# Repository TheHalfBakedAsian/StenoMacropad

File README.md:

# The Steno Macropad
**Note: in the journal some hours are logged on one day despite being done on differnt days because I didn't realise how this worked and waited**

The Steno-style macro-pad is designed to allow multiple keystrokes simultaneously to create new outputs. With conductive sensors, it creates a thin, portable *wired* macro-pad that still serves the functions of a much larger version.

### Code functionality
The keyboard works by taking all inputs from each of the capacitive sensors and filling in their respective states into a larger bitmap to compare to a predefined table of char arrays to print out to the keyboard. I made it using char arrays of characters, because I have had difficulties otherwise, and it's pretty nice for coding to have a quick list of all your common phrases when autocorrect fails.

### Hardware Choices
The traditional Macro-pad uses mechanical switches with 2 pins but is incredibly bulky and is much more prone to breaking. I opted to work with some capacitive touch sensors, which only need a copper pad to sense, with a Xiao Esp32 C3 for more ram/flash over an Arduino Pro Micro. The added flash allows me to code in more functions for the Macro-pad than the established Pro Micro. The UDFN/USON package of my sensor chip makes it smaller lets me get away with a smaller and thin pcb.

### Schematic design
Following the provided circuit plan from the data sheet of the IC, I wired the ***Steno Macro-Pad***

### PCB placing
Originally I wanted to keep **ALL** signal traces on one side, but the size of the PCB and other traces made it so I had to use some buried vias near the back side’s copper sense pads. But who can forget adding some personal symbol in the silk screening, mine being an ace of spades. alt text The large blue squares being the copper pads on the back side.  The large blue squares being the copper pads on the back side.

## Render

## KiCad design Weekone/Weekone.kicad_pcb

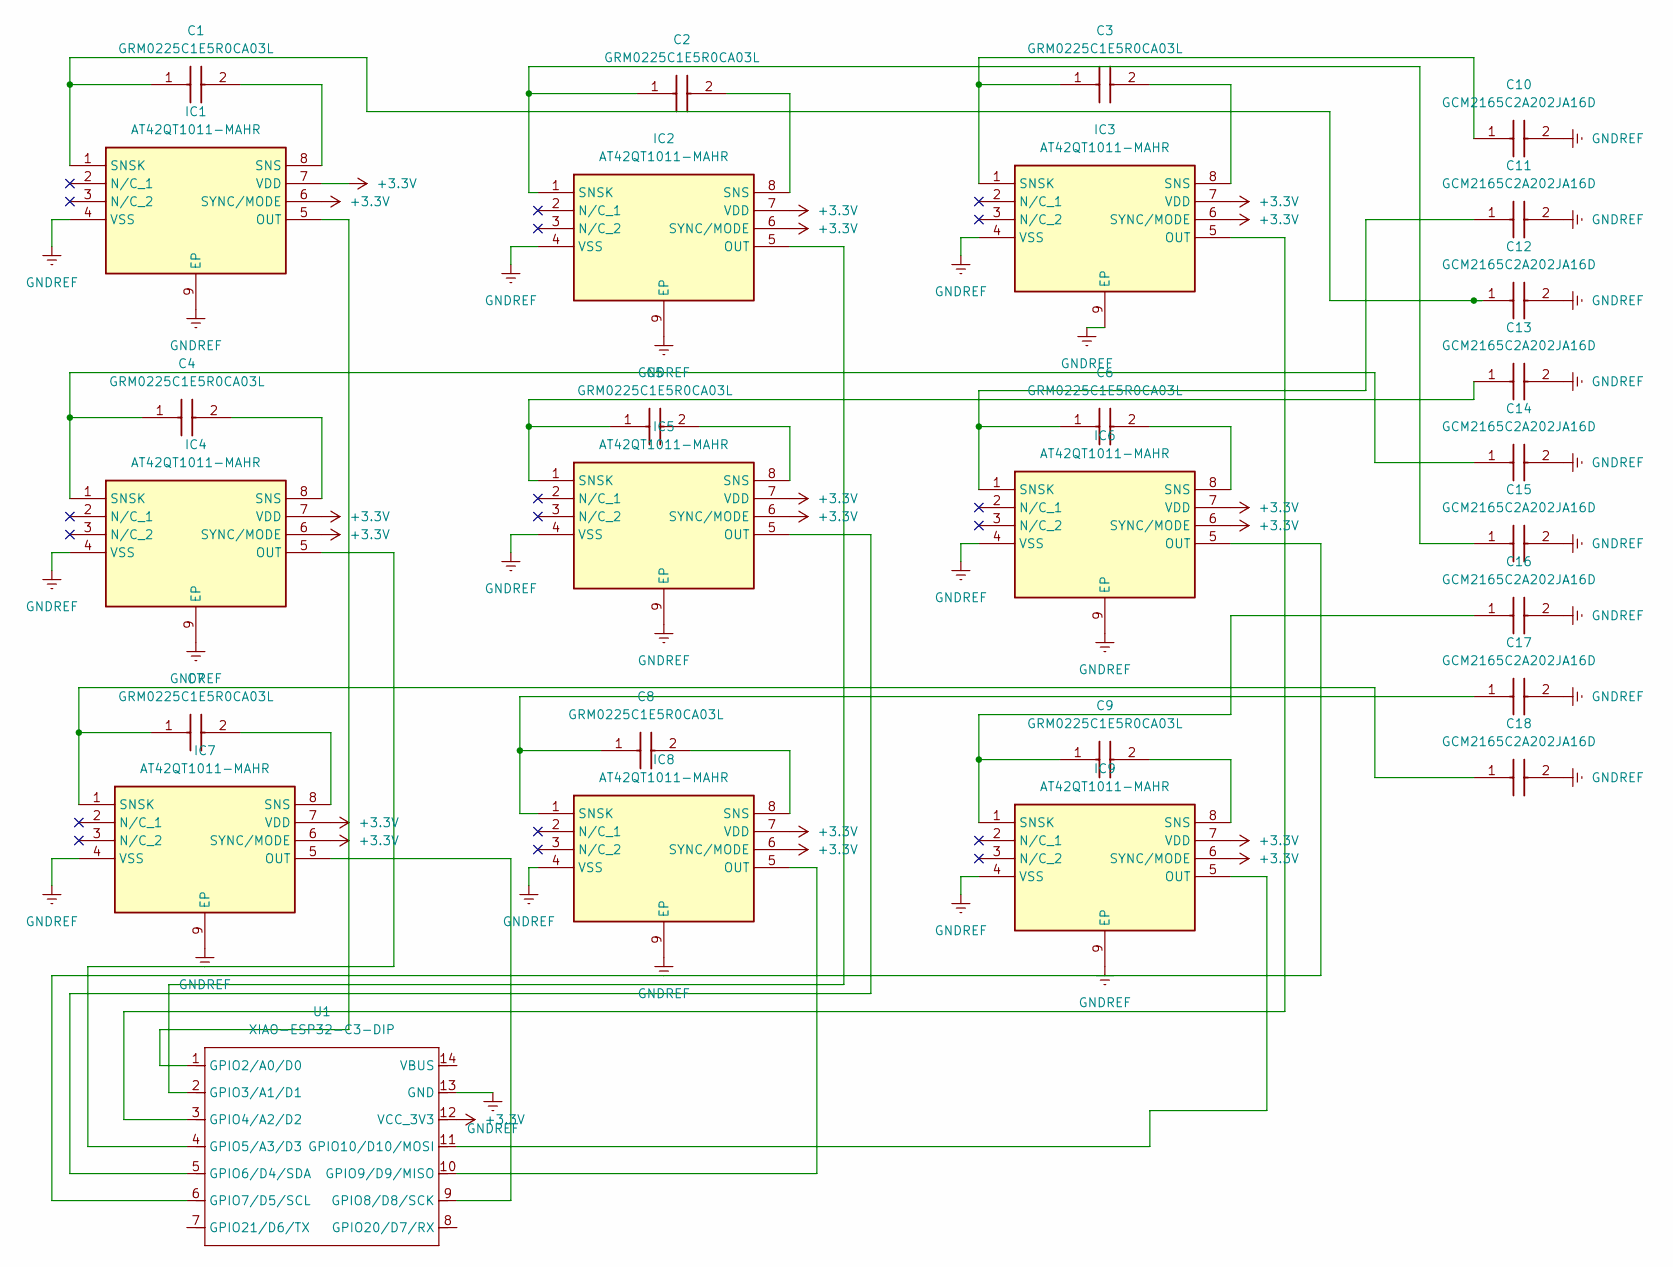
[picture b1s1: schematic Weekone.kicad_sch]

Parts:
C1, C2, C3, C4, C5, C6, C7, C8, C9: GRM0225C1E5R0CA03L; GRM022C81C222KE01L; Mouser Part Number 81-GRM0225C1E5R0CA3L
C10, C11, C12, C13, C14, C15, C16, C17, C18: GCM2165C2A202JA16D; GCM21; Manufacturer_Part_Number GCM2165C2A202JA16D
IC1, IC2, IC3, IC4, IC5, IC6, IC7, IC8, IC9: AT42QT1011-MAHR; SON50P200X200X60-9N; Mouser Part Number 556-AT42QT1011-MAHR
U1: XIAO-ESP32-C3-DIP; XIAO-ESP32S3-DIP

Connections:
+3.3V: IC1.6 (SYNC/MODE), IC1.7 (VDD), IC2.6 (SYNC/MODE), IC2.7 (VDD), IC3.6 (SYNC/MODE), IC3.7 (VDD), IC4.6 (SYNC/MODE), IC4.7 (VDD), IC5.6 (SYNC/MODE), IC5.7 (VDD), IC6.6 (SYNC/MODE), IC6.7 (VDD), IC7.6 (SYNC/MODE), IC7.7 (VDD), IC8.6 (SYNC/MODE), IC8.7 (VDD), IC9.6 (SYNC/MODE), IC9.7 (VDD), U1.12 (VCC_3V3)
GNDREF: C10.2, C11.2, C12.2, C13.2, C14.2, C15.2, C16.2, C17.2, C18.2, IC1.4 (VSS), IC1.9 (EP), IC2.4 (VSS), IC2.9 (EP), IC3.4 (VSS), IC3.9 (EP), IC4.4 (VSS), IC4.9 (EP), IC5.4 (VSS), IC5.9 (EP), IC6.4 (VSS), IC6.9 (EP), IC7.4 (VSS), IC7.9 (EP), IC8.4 (VSS), IC8.9 (EP), IC9.4 (VSS), IC9.9 (EP), U1.13 (GND)
unnamed: IC1.5 (OUT), U1.1 (GPIO2/A0/D0)
unnamed: C1.2, IC1.8 (SNS)
unnamed: C1.1, C12.1, IC1.1 (SNSK)
unnamed: IC2.5 (OUT), U1.2 (GPIO3/A1/D1)
unnamed: C2.2, IC2.8 (SNS)
unnamed: C2.1, C15.1, IC2.1 (SNSK)
unnamed: IC3.5 (OUT), U1.3 (GPIO4/A2/D2)
unnamed: C3.2, IC3.8 (SNS)
unnamed: C3.1, C10.1, IC3.1 (SNSK)
unnamed: IC4.5 (OUT), U1.4 (GPIO5/A3/D3)
unnamed: C4.2, IC4.8 (SNS)
unnamed: C4.1, C14.1, IC4.1 (SNSK)
unnamed: IC5.5 (OUT), U1.5 (GPIO6/D4/SDA)
unnamed: C5.2, IC5.8 (SNS)
unnamed: C5.1, C13.1, IC5.1 (SNSK)
unnamed: IC6.5 (OUT), U1.6 (GPIO7/D5/SCL)
unnamed: C6.2, IC6.8 (SNS)
unnamed: C6.1, C11.1, IC6.1 (SNSK)
unnamed: IC7.5 (OUT), U1.9 (GPIO8/D8/SCK)
unnamed: C7.2, IC7.8 (SNS)
unnamed: C7.1, C18.1, IC7.1 (SNSK)
unnamed: IC8.5 (OUT), U1.10 (GPIO9/D9/MISO)
unnamed: C8.2, IC8.8 (SNS)
unnamed: C8.1, C17.1, IC8.1 (SNSK)
unnamed: IC9.5 (OUT), U1.11 (GPIO10/D10/MOSI)
unnamed: C9.2, IC9.8 (SNS)
unnamed: C9.1, C16.1, IC9.1 (SNSK)

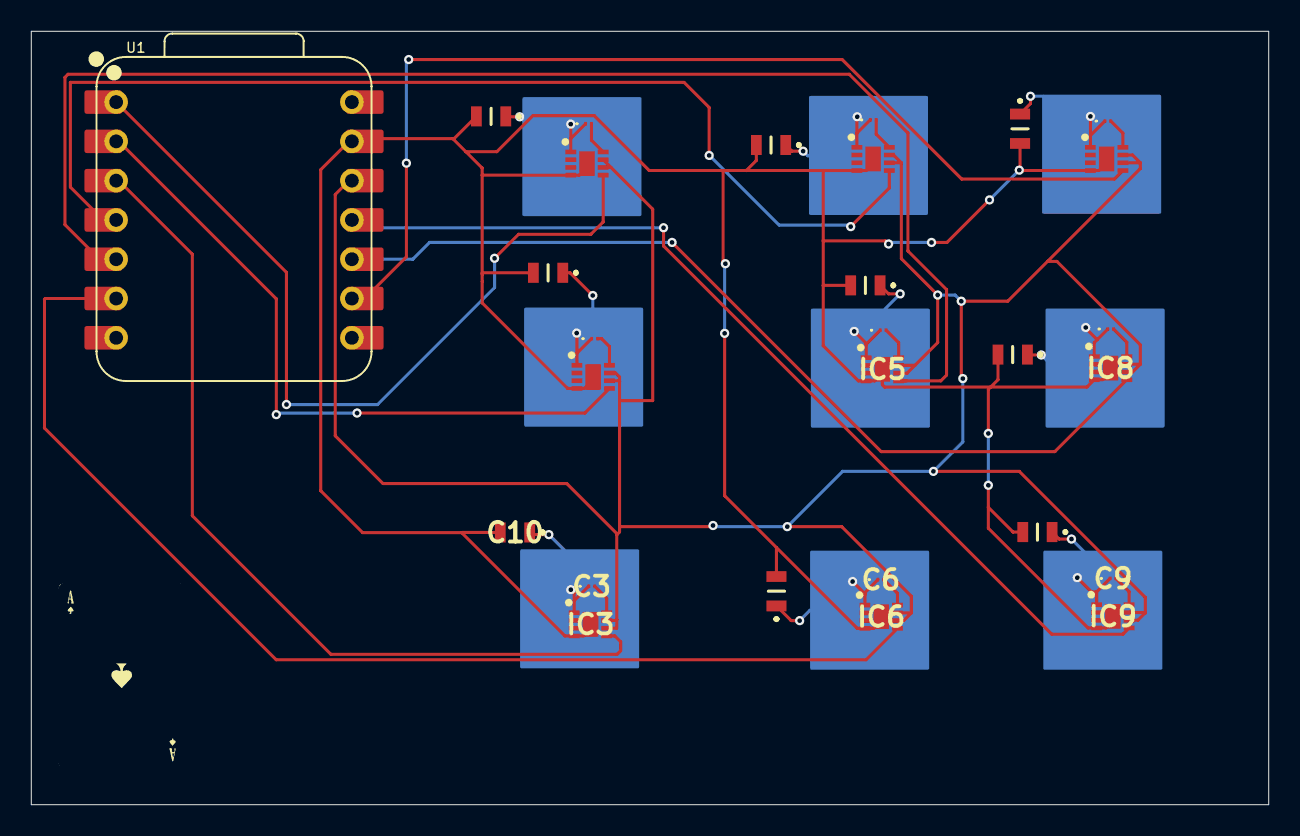
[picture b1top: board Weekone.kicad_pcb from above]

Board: 2 copper layers, 80.0 x 50.0 mm, 29 parts (0 on the bottom side), 29 nets.

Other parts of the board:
.: LOGO
